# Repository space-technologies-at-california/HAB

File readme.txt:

High Altitude Balloon Team
Space Technologies at Cal
University of California, Berkeley

We're currently working on HABV!

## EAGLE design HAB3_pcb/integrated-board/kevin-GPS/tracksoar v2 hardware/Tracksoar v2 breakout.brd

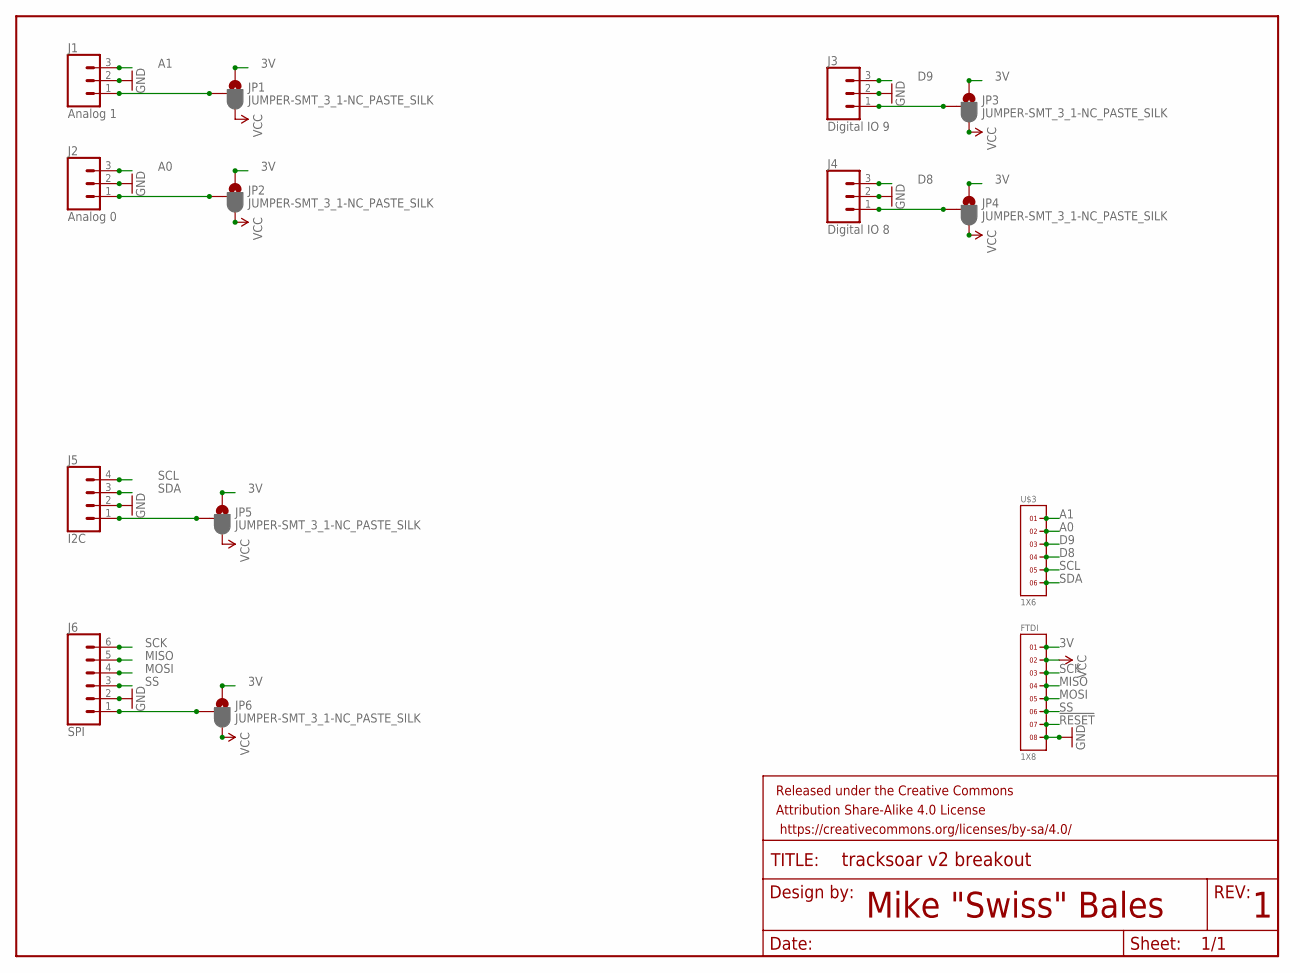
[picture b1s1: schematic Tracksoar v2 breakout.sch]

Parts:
FRAME1: FRAME-LETTER; CREATIVE_COMMONS
FTDI: 1X8
J1: Analog 1; 1X03_LONGPADS
J2: Analog 0; 1X03_LONGPADS
J3: Digital IO 9; 1X03_LONGPADS
J4: Digital IO 8; 1X03_LONGPADS
J5: I2C; 1X04_LONGPADS
J6: SPI; 1X06_LONGPADS
JP1, JP2, JP3, JP4, JP5, JP6: JUMPER-SMT_3_1-NC_PASTE_SILK; SMT-JUMPER_3_1-NC_PASTE_SILK
U$3: 1X6

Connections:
3V: FTDI.1, JP1.1, JP2.1, JP3.1, JP4.1, JP5.1, JP6.1
!RESET: FTDI.7
A0: J2.3, U$3.2
A1: J1.3, U$3.1
D8: J4.3, U$3.4
D9: J3.3, U$3.3
GND: FTDI.8, J1.2, J2.2, J3.2, J4.2, J5.2, J6.2
MISO: FTDI.4, J6.5
MOSI: FTDI.5, J6.4
unnamed: J1.1, JP1.2
unnamed: J2.1, JP2.2
unnamed: J3.1, JP3.2
unnamed: J4.1, JP4.2
unnamed: J5.1, JP5.2
unnamed: J6.1, JP6.2
SCK: FTDI.3, J6.6
SCL: J5.4, U$3.5
SDA: J5.3, U$3.6
SS: FTDI.6, J6.3
VCC: FTDI.2, JP1.3, JP2.3, JP3.3, JP4.3, JP5.3, JP6.3

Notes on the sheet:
Mike "Swiss" Bales

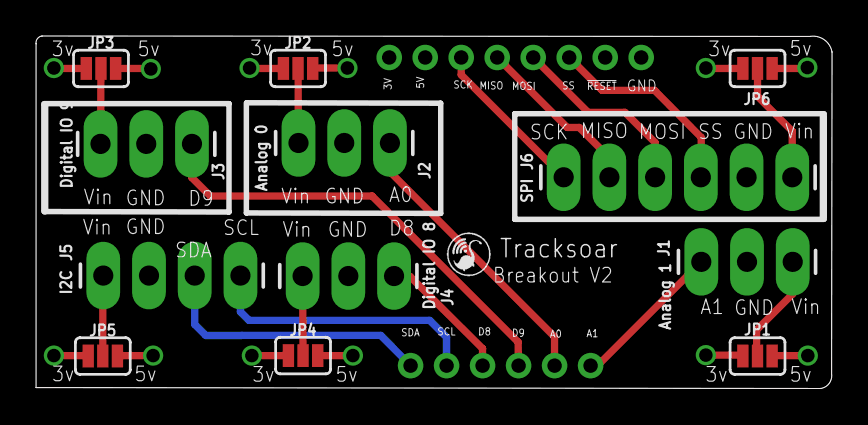
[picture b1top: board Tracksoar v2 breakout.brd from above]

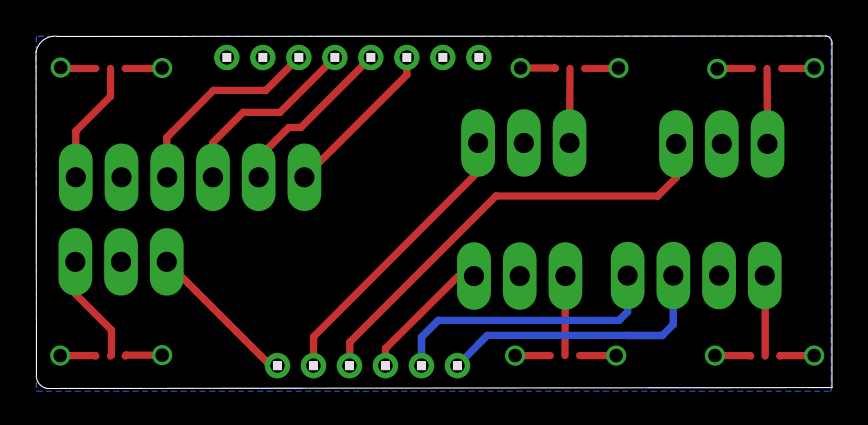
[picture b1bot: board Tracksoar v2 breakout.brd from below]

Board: 4 copper layers, 44.2 x 19.6 mm, 15 parts (2 on the bottom side), 19 nets.

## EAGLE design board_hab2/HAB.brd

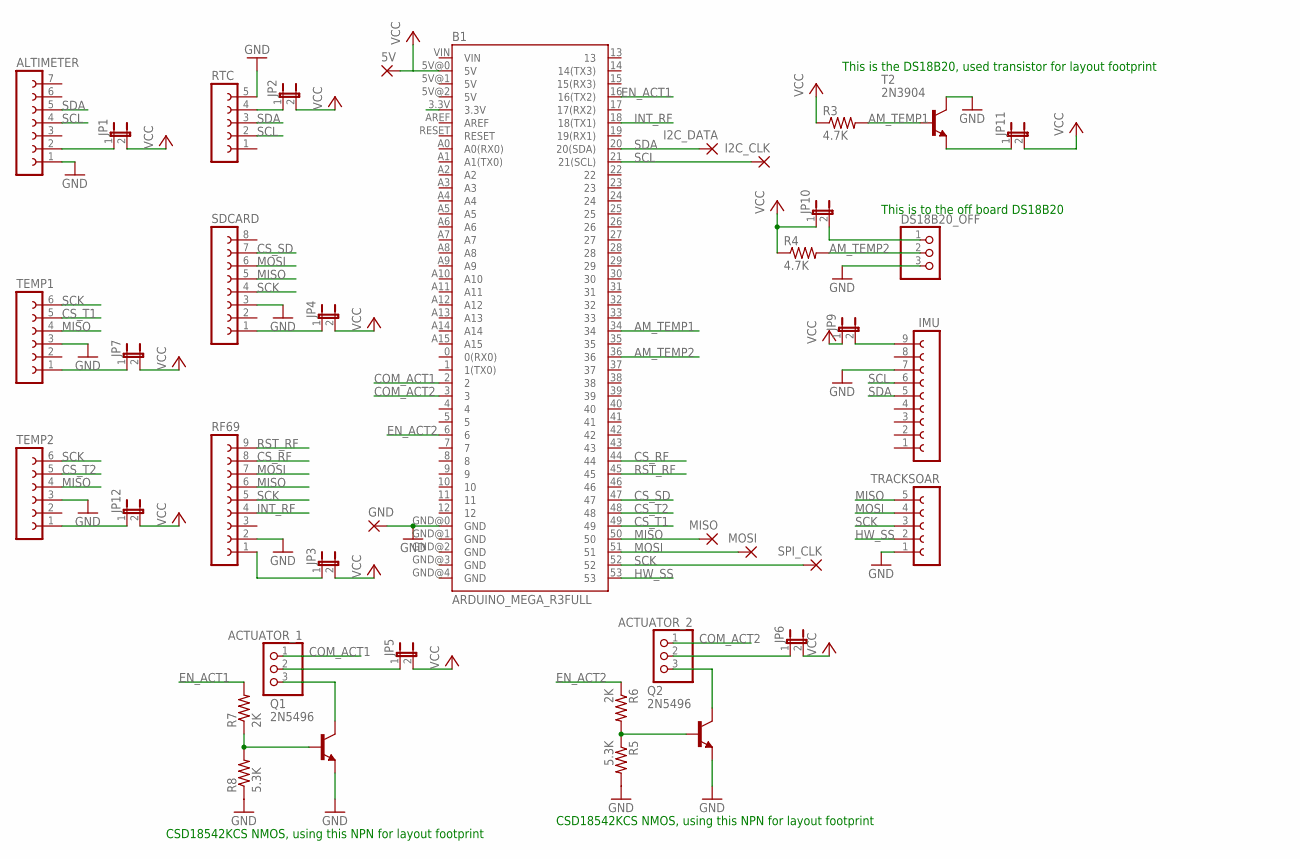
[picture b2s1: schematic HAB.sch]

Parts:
5V: 1,6/0,8
ACTUATOR_1, ACTUATOR_2: PINHD-1X3; 1X03
ALTIMETER: FE07-1; FE07
B1: ARDUINO_MEGA_R3FULL; ARDUINO_MEGA
DS18B20_OFF: PINHD-1X3; 1X03
GND: 1,6/0,8
I2C_CLK, I2C_DATA: 1,6/0,8
IMU: FE09-1; FE09
JP1, JP2, JP3, JP4, JP5, JP6, JP7, JP9, JP10, JP11, JP12: JP1E; JP1
MISO: 1,6/0,8
MOSI: 1,6/0,8
Q1, Q2: 2N5496; TO220
R3, R4: 4.7K; 0207/10
R5, R8: 5.3K; 0207/10
R6, R7: 2K; 0207/10
RF69: FE09-1; FE09
RTC: FE05-1
SDCARD: FE08-1; FE08
SPI_CLK: 1,6/0,8
T2: 2N3904; TO92
TEMP1, TEMP2: FE06-1; FE06
TRACKSOAR: FE05-1

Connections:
AM_TEMP1: B1.34, R3.2, T2.2 (B)
AM_TEMP2: B1.36, DS18B20_OFF.2, R4.2
COM_ACT1: ACTUATOR_1.1, B1.2
COM_ACT2: ACTUATOR_2.1, B1.3
CS_RF: B1.44, RF69.8
CS_SD: B1.47, SDCARD.7
CS_T1: B1.49, TEMP1.5
CS_T2: B1.48, TEMP2.5
EN_ACT1: B1.16 (16(TX2)), R7.2
EN_ACT2: B1.6, R6.1
GND: ALTIMETER.1, B1.GND@0 (GND), DS18B20_OFF.3, GND.1, IMU.7, Q1.3 (E), Q2.3 (E), R5.2, R8.1, RF69.2, RTC.5, SDCARD.3, T2.1 (C), TEMP1.3, TEMP2.3, TRACKSOAR.1
HW_SS: B1.53, TRACKSOAR.2
INT_RF: B1.18 (18(TX1)), RF69.4
MISO: B1.50, MISO.1, RF69.6, SDCARD.5, TEMP1.4, TEMP2.4, TRACKSOAR.5
MOSI: B1.51, MOSI.1, RF69.7, SDCARD.6, TRACKSOAR.4
unnamed: Q2.1 (B), R5.1, R6.2
unnamed: DS18B20_OFF.1, JP10.2
unnamed: ACTUATOR_2.3, Q2.2 (C)
unnamed: Q1.1 (B), R7.1, R8.2
unnamed: ACTUATOR_1.3, Q1.2 (C)
unnamed: JP3.1, RF69.1
unnamed: JP7.1, TEMP1.1
unnamed: JP12.1, TEMP2.1
unnamed: ALTIMETER.2, JP1.1
unnamed: JP2.1, RTC.4
unnamed: JP4.1, SDCARD.1
unnamed: ACTUATOR_1.2, JP5.1
unnamed: ACTUATOR_2.2, JP6.1
unnamed: IMU.9, JP9.2
unnamed: JP11.1, T2.3 (E)
RST_RF: B1.45, RF69.9
SCK: B1.52, RF69.5, SDCARD.4, SPI_CLK.1, TEMP1.6, TEMP2.6, TRACKSOAR.3
SCL: ALTIMETER.4, B1.21 (21(SCL)), I2C_CLK.1, IMU.6, RTC.2
SDA: ALTIMETER.5, B1.20 (20(SDA)), I2C_DATA.1, IMU.5, RTC.3
VCC: 5V.1, B1.5V@0 (5V), JP1.2, JP2.2, JP3.2, JP4.2, JP5.2, JP6.2, JP7.2, JP9.1, JP10.1, JP11.2, JP12.2, R3.1, R4.1

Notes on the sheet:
This is the DS18B20, used transistor for layout footprint
CSD18542KCS NMOS, using this NPN for layout footprint
This is to the off board DS18B20

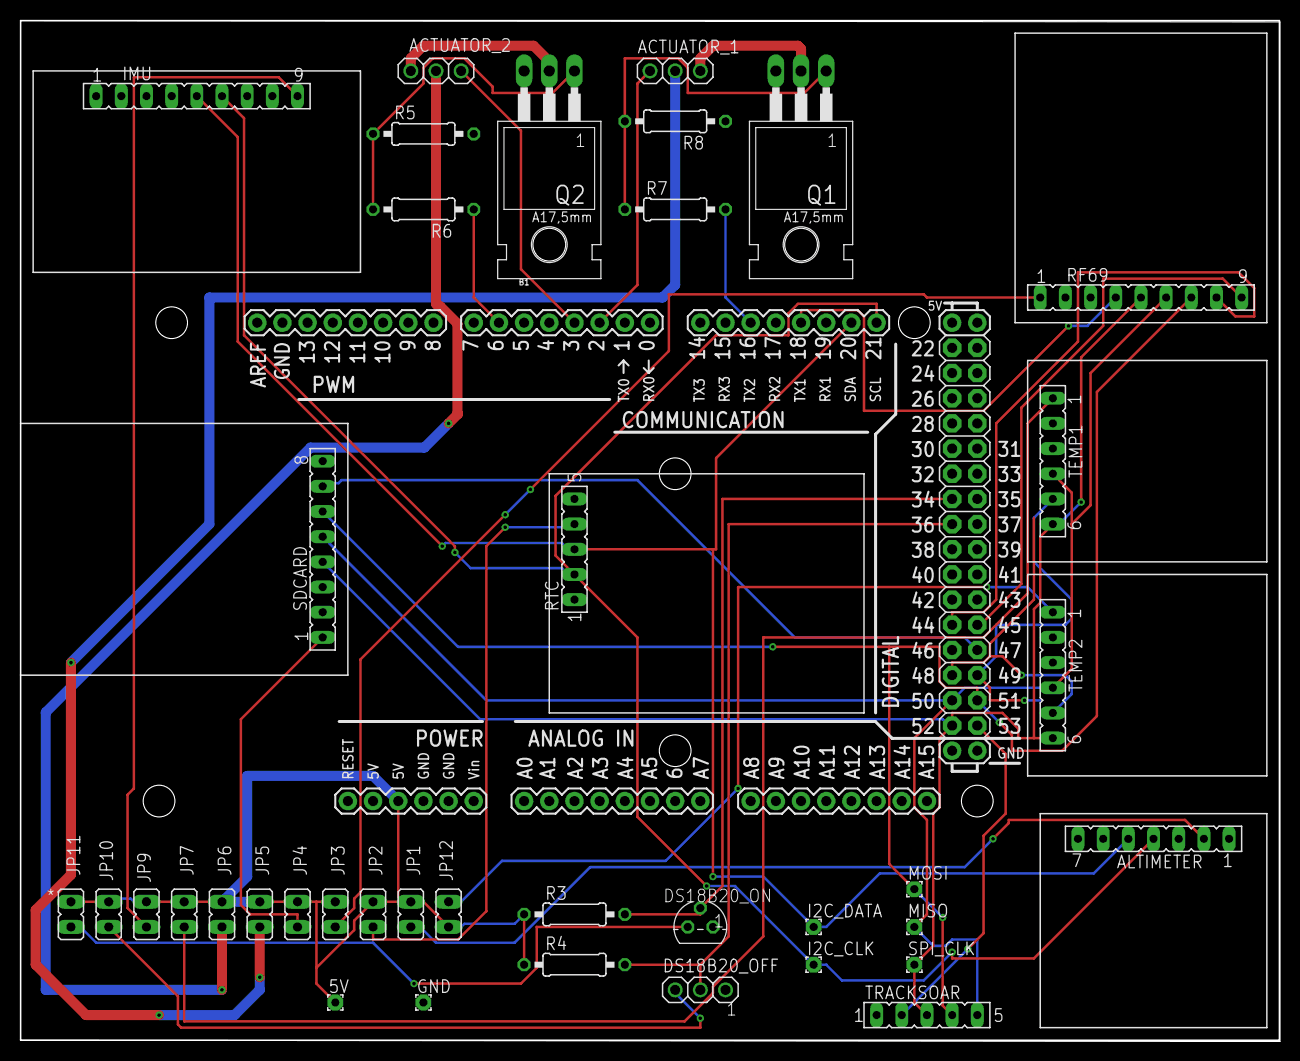
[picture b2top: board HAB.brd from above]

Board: 2 copper layers, 127.0 x 102.9 mm, 39 parts (0 on the bottom side), 35 nets.

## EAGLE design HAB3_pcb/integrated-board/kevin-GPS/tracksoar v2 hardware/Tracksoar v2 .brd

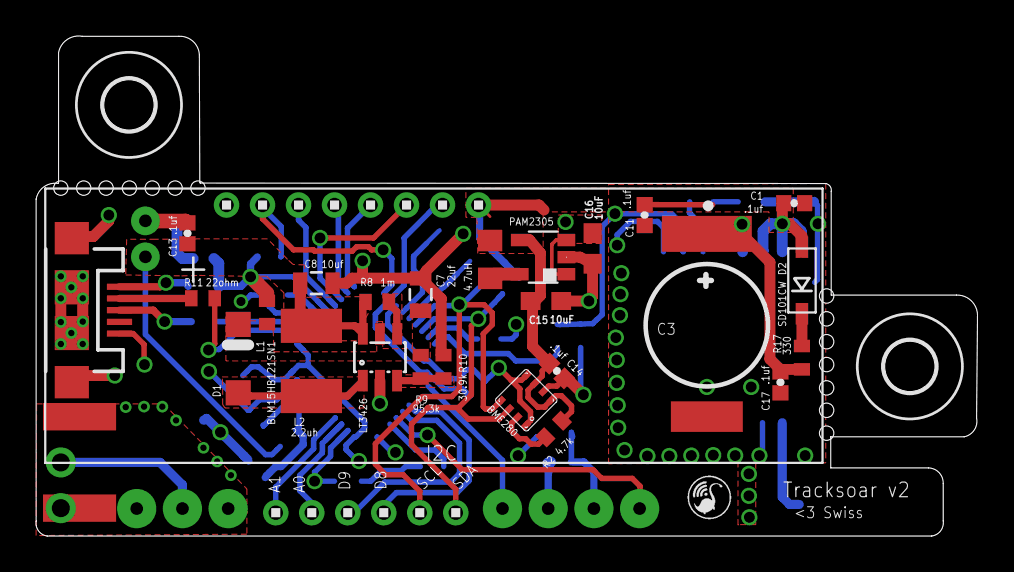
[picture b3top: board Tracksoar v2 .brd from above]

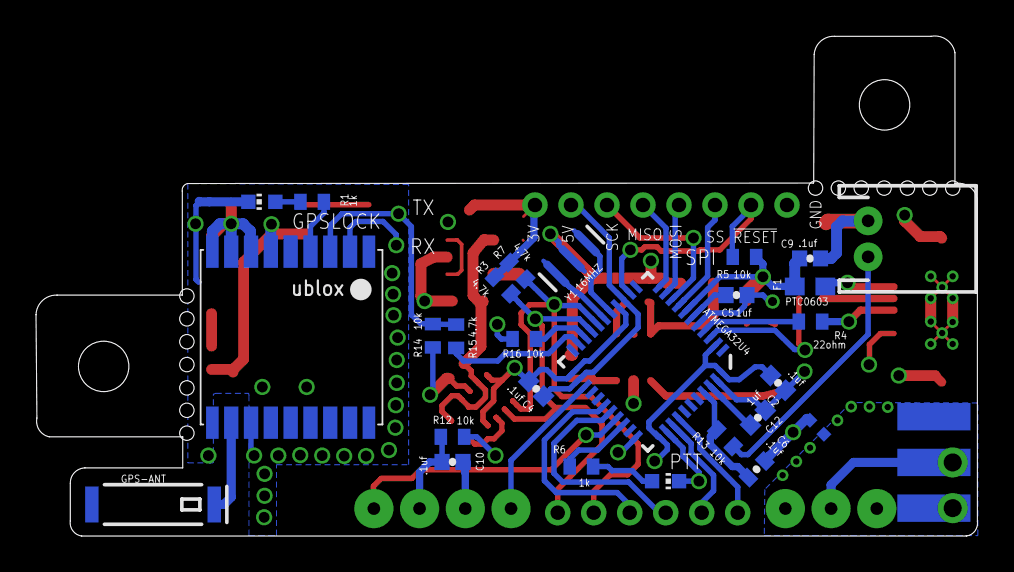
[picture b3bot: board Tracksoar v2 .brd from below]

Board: 4 copper layers, 52.3 x 27.8 mm, 59 parts (28 on the bottom side), 47 nets.

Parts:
C1, C2, C4, C6, C9, C10, C11, C13, C14, C17: .1uf; 0402-CAP
C3: GPS BACKUP; DSK-3R3H204T614-H2L
C5, C12: 1uf; 0402-CAP
C7: 22uf; 0805
C8: 10uf; 0805
C15, C16: 10uF; 0603
D1: MBR120VLSFT1; SOD123
D2: SD101CW; SOD-123
F1: PTC0603; 0603
FRAME1: FRAME-LETTER; CREATIVE_COMMONS
FTDI: 1X8
GPS-ANT: 1.575GHz; ANT-GPS-2X7MM
GPSLOCK: CHIP-LED0603
H1, H2: MOUNT-HOLE2.8; 2,8
IC1: BME280
J1: battery; JST-2-PTH
J$1: SMA_EDGE; SMA-EDGE
JP1: USB-MICROB
L1: BLM15HB121SN1; 0402
L2: 2.2uh; L1812
LT3426: LT3426; SOT23-6
PTT: CHIP-LED0603
R1, R6: 1k; R0402
R2, R3, R7, R15: 4.7k; R0402
R4, R11: 22ohm; R0402
R5, R12, R13, R14, R16: 10k; R0402
R8: 1m; R0402
R9: 95.3k; R0402
R10: 30.9k; R0402
R17: 330; R0402
U$1: UBLOX_MAX
U$2: RADIOMETRIX-HX1
U$3: 1X6
U$4: ATMEGA32U4; QFN-44-NOPAD
U$5: PAM2305; DBV_R-PDSO-G5
U$6: 4.7uH; RESC0805_N
U$7: RESC0402_N
Y1: 16MHZ; RESONATOR-SMD

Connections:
3V: C1.2, C11.2, C14.2, C15.1, D2.A, FTDI.1, IC1.6, IC1.8, R2.1, R3.1, R7.1, U$1.7_VCC_IO, U$1.8_VCC, U$1.9_V_RESET, U$5.4, U$6.1
!RESET: FTDI.7, R5.1, U$4.13
A0: U$3.2, U$4.36
A1: U$3.1, U$4.37
D3: U$2.TXD, U$4.30
D4: U$2.EN, U$4.25
D8: U$3.4, U$4.28
D9: U$3.3, U$4.29
D+: R4.2, U$4.4
D-: R11.2, U$4.3
GND: C1.1, C2.1, C3.2, C4.1, C5.1, C6.1, C7.2, C8.2, C9.1, C10.1, C11.1, C12.1, C13.1, C14.1, C15.2, C16.2, C17.1, FTDI.8, GPSLOCK.C, IC1.1, IC1.5, IC1.7, J1.1, JP1.GND, JP1.MT1, JP1.MT2, LT3426.2, PTT.C, R10.1, R12.1, R14.2, U$1.1_GND, U$1.10_GND, U$1.12_GND, U$2.0V, U$4.5, U$4.15, U$4.23, U$4.35, U$4.43, U$5.2, U$7.1, Y1.2
HWB: R12.2, U$4.33
LED: R6.2, U$4.31
MISO: FTDI.4, U$4.11
MOSI: FTDI.5, U$4.10
unnamed: J$1.SIG, U$2.RFOUT
unnamed: IC1.2, R2.2
unnamed: GPSLOCK.A, R1.2
unnamed: GPS-ANT.1, U$1.11_RF_IN
unnamed: JP1.D-, R11.1
unnamed: JP1.D+, R4.1
unnamed: D1.A, L2.2, LT3426.1
unnamed: LT3426.4, R8.1
unnamed: LT3426.3, R9.1, R10.2
unnamed: F1.1, JP1.VBUS
unnamed: C12.2, U$4.42
unnamed: C7.1, D1.C, L1.1, LT3426.5, R9.2
unnamed: C5.2, U$4.6
unnamed: U$5.5, U$6.2
unnamed: D2.C, R17.1
unnamed: PTT.A, R6.1
PPS: R1.1, U$1.4_TIMEPULSE
RFGND: J$1.GND@0, J$1.GND@1, J$1.GND@2, J$1.GND@3, U$2.RFGND, U$2.RFGND2, U$7.2
RX: R16.1, U$4.20
RX1: R16.2, U$1.2_TXD1
SCK: FTDI.3, U$4.9
SCL: IC1.4, R7.2, U$3.5, U$4.18
SDA: IC1.3, R3.2, U$3.6, U$4.19
SS: FTDI.6, U$4.8
TX: R15.2, U$4.21
TX1: R14.1, R15.1, U$1.3_RXD1
VBACKUP: C3.1, C17.2, R17.2, U$1.6_V_BCKP
VCC: C2.2, C4.2, C9.2, C10.2, C16.1, F1.2, FTDI.2, L1.2, R5.2, U$2.VCC, U$4.2, U$4.7, U$4.14, U$4.24, U$4.34, U$4.44, U$5.1, U$5.3
VIN: C8.1, C13.2, J1.2, L2.1, LT3426.6, R8.2, R13.1
VSENSE: C6.2, R13.2, U$4.41
XTAL1: U$4.17, Y1.1
XTAL2: U$4.16, Y1.3

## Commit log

2016-11-03 08 March Tues
2018-02-15 rf69 libraries
2018-02-15 added readme
2018-02-15 rf69 beacon/receiver testing code ready
2018-02-15 radiohead lib was empty
2018-02-15 updated radiohead lib readme
2018-02-15 migrated jpole_sim repo to here
2018-02-18 tested RF69 transmitter
2018-02-22 started range test code for rf69
2018-02-23 chat_demo ready to test
2018-02-23 fixed chat demo, dynamic mem allocation problem
2018-02-23 memory allocation within function vs global is different; uint8_t does not reserve 8 bits
2018-02-24 embedded sys code
2018-02-24 added thermocoupling
2018-02-24 2ndary transmitter for balloon ready for integration
2018-02-24 deleted empty RadioHead folder
2018-02-24 changed rf69 pins to mega pins
2018-02-25 hey abhi
2018-02-25 LED_debug_bank added
2018-02-25 altimeter code added
2018-02-25 really ugly code
2018-02-25 added altimeter
2018-02-25 ...it worked ;)
2018-02-25 wiring diagram 60%
2018-02-25 added libraries
2018-02-25 updated arduino alt code
2018-02-25 put RadioHead-master.zip back
2018-02-26 finished wiring diagram
2018-02-26 Changed servo pins, wrote experiment code to extend both servos (needs to be tested) and wrote servo extended to log
2018-02-28 added 2ndary transceiver
2018-02-28 changed transceiver CS pin from pin 46 to pin 44
2018-02-28 added 2nd order temp and fixed barometric eq
2018-02-28 Rewrote and tested servo code on hardware
2018-03-01 adding tracksoar source code
2018-03-01 adding preliminary untested code to do spi comm with tracksoar from Mega
2018-03-02 updated HAB_Sys
2018-03-02 changed todo
2018-03-02 added tracksoar and transceiver code independently, need to integrate the two
2018-03-02 added edge cases todo in comments
2018-03-02 changed SD & thermoCS pin
2018-03-02 SD, thermo, all i2c working
2018-03-02 hopefully added stuff
2018-03-02 fixing error in tracksoar code
2018-03-02 playing with servos
2018-03-02 servo code pre-test
2018-03-02 testing servos
2018-03-02 tested all but servo lock on timeout
2018-03-02 added tracksoar -> transceiver code
2018-03-03 changing tracksoar comm to shut off spi after comms
2018-03-03 SPI tracksoar init HIGH, ty Alan
2018-03-03 servo disable example
2018-03-03 servo_disable_test & rf69_stac fixes
2018-03-03 fixing tracksoar spi issue
2018-03-03 committing to fix merge issue in HAB_sys
2018-03-03 added tracksoar data store, servo fet disable
2018-03-03 serial python altimeter test script
2018-03-03 minor servo changes
2018-03-04 added get gps lock spi fix
2018-03-04 updated serial alt test
2018-03-04 fixing issue in tracksoar comm library
2018-03-04 CS tracksoar
2018-03-04 gps lock spi
2018-03-04 altitude test
2018-03-04 deleted extra print statements
2018-03-04 added raw altimeter bits to CSV
2018-03-04 added one line
2018-03-04 Add files via upload
    lat, long to degrees, minutes, seconds
    optional offline coordinate finder
2018-03-04 final
2018-03-04 Deleted Serial while loop
2018-03-05 adding APRS.fi data dumps to git
2018-03-07 added decoder for aprsdroid
2018-03-20 Add files via upload
    Script for the intervalometer used with hacked Canon Powershot A3100
2018-04-12 data
2018-04-12 commenting code
2018-04-13 added Eagle files for HAB-2
2018-04-13 updated gitignore and added comments to HAB board
2018-04-14 Removed .DS_Store file and changed board schematics
2018-04-14 finished schematic
2018-04-14 fixed missing servo enable connetion
2018-04-14 placed and routed hab board
2018-04-15 Added gerbers and updated thick trace
2018-04-15 removed extra files
2018-04-15 final changes
2018-04-15 arduino example for one wire reading... requires one wire and temp libraries
2018-04-21 code moved to experiment
2018-04-21 refactoring done
2018-04-22 1 servo only
2018-04-26 Added ambient temperature sensor measuring code to Hab Sys
2018-04-27 added imu setup code
2018-04-27 all sensors added
2018-10-11 Add Hab3 PCB folder
2018-10-11 adding IMU KiCa
2018-10-11 added altimeter pcb
2018-10-11 started tracing
2018-10-16 traces done without copper fills
2018-10-16 moved folder and need to add copper fills still
2018-10-18 updated labels on riley's pcb
2018-10-18 added labels and made board have 4 layers
2018-10-18 init commit for tim-mcu-sd-power
2018-10-18 moved rtc into master
2018-10-18 Final PCB IMU
2018-10-18 halfway done with power regulator
2018-10-22 changed diodes to be SOD 123 and updated footprint
2018-10-23 Finished voltage regulator
2018-10-23 Integrated board complete
2018-10-25 had to literally redo everything
2018-10-26 integrated board with new imu-dfm complete
2018-10-28 made fixes to new imu
2018-10-29 added tracksoar eagle files
2018-10-29 convert tracksoar to kicad
2018-10-29 changed schematic and footprint following design review
2018-10-29 changed footprints to be hand-soldered style
2018-10-29 changed fonts to be thicker, 0402 -> 0603_hand_solder
2018-10-29 fixed gps board
2018-10-29 fixed power on integrated board
2018-10-29 final pcb designs complete
2018-10-29 final pcb design complete with InstantDFM
2018-10-29 final final pcb design complete with InstantDFM
2018-11-13 fix typos in TempControl.ino
2018-12-02 add flight code hab3
2018-12-02 finish hab3 flight code
2018-12-03 print data recorded to serial flight_code
2018-12-03 add rockblock antenna select
2018-12-03 add zip libraries to flight code
2018-12-03 fix get signal quality bug
2018-12-03 add more printlns to flight code
2018-12-03 webapp
2018-12-03 final changes to flight code
2019-02-02 update flight code
2019-02-23 commit unsaved changes
2019-02-23 put all schematics into HABIV
2019-02-23 habiv integrated schematic w/o power
2019-02-23 add some hardwired connections
2019-03-02 some habiv schematic changes
2019-03-02 implemented IMU power and ground connection with decoupling caps
2019-03-02 SD Card connections
2019-03-02 implemented 0 ohm resistors on Vdd pins of ICs, continue to implement 0 ohms on SPI and I2C pin
2019-03-02 finished implementing 0 ohm resistors on clock pins
2019-03-02 IMU SDA and SCL pins connected to MCU
2019-03-03 some small fixes to schematic
2019-03-09 remove the pin headers to clean up the schematic; added 0 ohm connection from GPS FIX to PB15
2019-03-10 footprint layouts for capacitors and resistors
2019-03-16 change power converter output format
2019-03-16 link more footprints
2019-03-20 test out layouts for different sections
2019-03-20 get pcb design out of old
2019-04-02 add old_board_submodules and complete all but tim
2019-04-02 finish submodules and combine
2019-04-02 layout for imu
2019-04-06 fix power system layout on habiv
2019-04-06 clean up silkscreen
2019-04-06 fix gps and fix imu connections
2019-04-06 begin to route together final nets
2019-04-06 finish most of connections for 4 layer
2019-04-17 finalize rough draft board
2019-04-19 fix drc stuff for layout
2019-04-20 spread out some imu conns
2019-04-20 change hole positions
2019-04-20 fix some references
2019-04-20 fix some schematic errorS
2019-04-20 some work on layout redo
2019-04-24 :art: Fix layout connections for new schematic
2019-04-27 add back ground plane
2019-04-27 fix all drc errors
2019-04-27 add xt30 connectors
2019-05-04 add servo breakouts
2019-05-04 add breakouts for rockblock and relay
2019-05-04 add final 5v conn
2019-09-13 finsished hw2
2019-09-18 Revert "add final 5v conn"
    This reverts commit 04f0e62ac933d6a4970588d5189f4c859ce7453e.
2019-09-18 Removed false file
2019-09-22 add noise reducing caps and fix unconnected in1 plane
2019-09-22 update silkscreen text
2019-09-22 copied hab3 code to a HABIV file.
2019-09-22 Create Semi_Controlled
2019-09-22 Create newfile
2019-09-23 added basic comments.
2019-09-25 added IMU library zip
2019-10-02 added comments about what board to use.
2019-10-02 added IMU declarations and Setup.
2019-10-06 integrated IMU with pre-existing getAllData function.
2019-10-09 set imu as I2C
2019-10-19 added one servo for testing.
2019-10-23 added basic servo control with the XBee.
2019-10-25 added example sketch for showing how to control servo from XBee input.
2019-10-31 set up XBee code for running the servo control.
2019-11-03 updated getXBeeControl()
2019-11-07 added value for release.
2019-11-08 configure data for rockblock
2019-11-08 flip lat and long
2019-11-10 bug fixes, now compiles.
2019-11-11 gen stencil
2019-11-17 documentation
2019-11-17 added basic ground control code.
2019-11-17 short test onboard.
2019-11-22 renamed some files, updated hab4 code
2019-11-23 change pins
2020-02-02 deleted tracksoar
2020-02-05 fixing integrated board naming problem
2020-02-10 Turned IMU into breakout pins, minor changes, unfinished!
2020-02-11 Changed IMU pinout, fixed some grounding issues
2020-02-12 Moved RockBlock Connector, removed some Servo breakouts
2020-02-14 Added jumpers+ Rerouting
    Added Jumpers to schematic. Rerouted trace PB10 from J20 as it was generating a design rules error. Also placed some jumpers on board.
2020-02-14 Updates for rn
2020-02-14 JP on RTC
2020-02-14 Added all jumpers
2020-02-15 double checked
2020-02-15 double check 2
2020-02-15 whoops, needed to move via
2020-02-19 did some clean-up, then added a latlong distance calculator.
2020-02-19 more cleaning, latlong update.
2020-02-23 split up the code into multiple tabs, more organized.
2020-02-23 renamed, reordered, now compiles.
2020-02-24 changed order again, added motor info.
2020-03-04 added beginning of UVB file. Updated names accordingly.
2020-03-04 forgot to add controls file.
2020-03-08 added library for I2C, integrated the UVB sensor in the rest of methods.
2020-03-08 updated sensor information with the new library and I2C.
2020-11-17 prepped code for off-loading controls to different processor.
2021-04-14 first commit adding HABV
2021-04-14 added test blinker.
2021-10-03 added HABV
2021-10-10 Added web app
2021-10-17 Added rockblock.py
2021-10-17 Added main_loop.py (Work in progress...)
2021-10-17 HABV BOARD 2
2021-10-27 Unable to plot point
2021-10-31 Web app: added point-plotting ability
2021-10-31 Added functionality for plotting multiple points
2021-10-31 Attempted to add overlay feature
2021-11-07 RockBlock code works and has been tested using USB Serial.
2021-11-14 Skeleton backend code
2021-11-14 Fixed some bugs in the template
2021-11-17 Web app: added template overlays
2021-11-17 Servo control code works. Can be imported as a function.
2022-01-30 2D PID Basic setup
2022-01-30 test.
2022-02-06 timers.
2022-02-06 Updated files
2022-02-06 Added lambda code
2022-02-20 Updated code
2022-02-27 Added beagle bone's local code into v2
2022-02-27 Updated Creds
2022-02-27 Saving HABV
2022-02-27 Changed to PST
2022-02-27 Updated code locally
2022-02-27 Removed test file
2022-02-27 Removed old files/folders
2022-02-28 Removed files
2022-03-16 added test file for aws
2022-03-27 Saving HABV prototype
2022-04-03 Saving PID flight code
2022-04-03 Saving flight code
2022-04-03 Saving flightcode
2022-04-10 Main_loop works but needs to be tested
2022-04-12 Changes to servo setting
2022-10-30 New files
2022-10-30 Added PID, traj_gen
2022-11-09 Added trajectory simulator and gps simulator
2022-11-09 Added historical NASA data
2022-11-13 Updated traj_gen
2022-11-16 Updated PID and input simulator, Added main
2022-11-16 Updated input simulator
2022-11-18 added environment class
2022-11-18 Cleaned up some code in environment.py
2022-11-20 WIP TrajGen
2022-11-27 TrajGen first iteration
2022-11-27 Refactored phase 0 and phase 1 parts
2022-11-27 Minor fixes and refactoring re phase 2
2022-11-27 Docstring fixes
2022-12-18 debugged, made working prototype
2023-01-04 Revised TrajGen
2023-01-05 Cleanup and updated phase 3

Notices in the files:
parts and their libraries:
SparkFun-PowerIC: Licensing: Creative Commons ShareAlike 4.0 International - https://creativecommons.org/licenses/by-sa/4.0
SparkFun-Aesthetics: Released under the Creative Commons Attribution Share-Alike 4.0 License
SparkFun-Aesthetics: https://creativecommons.org/licenses/by-sa/4.0
